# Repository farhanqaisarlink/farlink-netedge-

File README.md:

# FarLink

FarLink is a network performance monitoring platform built on the Raspberry Pi Compute Module 5 (CM5). It ships as two hardware variants that share a single codebase, plus a central dashboard server.

---

## Devices

### FarLink Go — with screen & push button

- On-demand speed test triggered by a push button; result shown on a 3.2" display
- Screen shows **only** the button-triggered speed test result — no other test output is displayed on-device
- Networking: DHCP by default, with a manual static IP option (`network_mode: dhcp | static`)
- Speed test engine: self-hosted **LibreSpeed** (configurable server address — no Ookla/speedtest.net, due to commercial licensing restrictions)
- Additional diagnostics (server-logged only, not shown on screen): `mtr`, `dig`, `curl`, `openssl`, `ping`, TCP port check
- Server can set a periodic test interval (15 min / 1 hour / 24 hours) in addition to the manual button trigger
- Results are saved locally with a timestamp; the server fetches the result file whenever the device is reachable and idle
- Device registers with the server

### FarLink Edge — headless, no screen or button

- Two units operate in **master/slave** configuration, running `iperf3` between them over a dedicated point-to-point link
- Physical connectivity: onboard RJ45 (ETH1) is used for uplink to the dashboard/internet; a USB-to-Ethernet adapter provides the dedicated master/slave link
- Same diagnostic suite as Go: `iperf3` (throughput / jitter / loss / retransmissions), `mtr`, `dig`, `curl`, `openssl`, `ping`, TCP port check
- Test schedule is set by the server; execution happens on the device
- Results are saved locally with a timestamp; the server fetches the result file whenever the device is reachable and idle
- Device registers with the server

### Shared codebase

Both devices run from **one common script**, not separate codebases. Hardware-specific behavior — screen output, push-button trigger, iPerf3 master/slave role — is enabled or disabled through configuration, so the same software runs on either hardware variant depending on which features are present.

---

## Server

- Receives device registrations and assigns device IDs
- Sets the periodic test interval (Go) or test schedule (Edge) per device
- Fetches each device's result file when the device is reachable and idle
- Combines fetched data into a report containing device ID, name, time, and per-test results

---

## Test tools

| Tool | Purpose |
|---|---|
| `librespeed-cli` | Internet speed test (Go) |
| `iperf3` | Throughput / jitter / loss / retransmissions, master/slave (Edge) |
| `mtr` | Path tracing |
| `dig` | DNS resolution timing |
| `curl` | HTTP/HTTPS response time |
| `openssl` | SSL/TLS certificate check |
| `ping` | ICMP latency |
| Python `socket` | TCP port reachability |

Install: `apt install iperf3 mtr dnsutils curl openssl`

---

## Hardware

- Raspberry Pi Compute Module 5 (non-wireless), single Gigabit Ethernet (RJ45), USB-C power, 3.2" ILI9341 display (Go only)
- Non-wireless CM5 is used deliberately to keep FCC/CE certification in the lower-cost unintentional-radiator path

---

## Out of scope for this phase

- ZTP provisioning / auto-registration beyond basic device registration
- AI-generated report summaries
- Ookla / speedtest.net as a test engine

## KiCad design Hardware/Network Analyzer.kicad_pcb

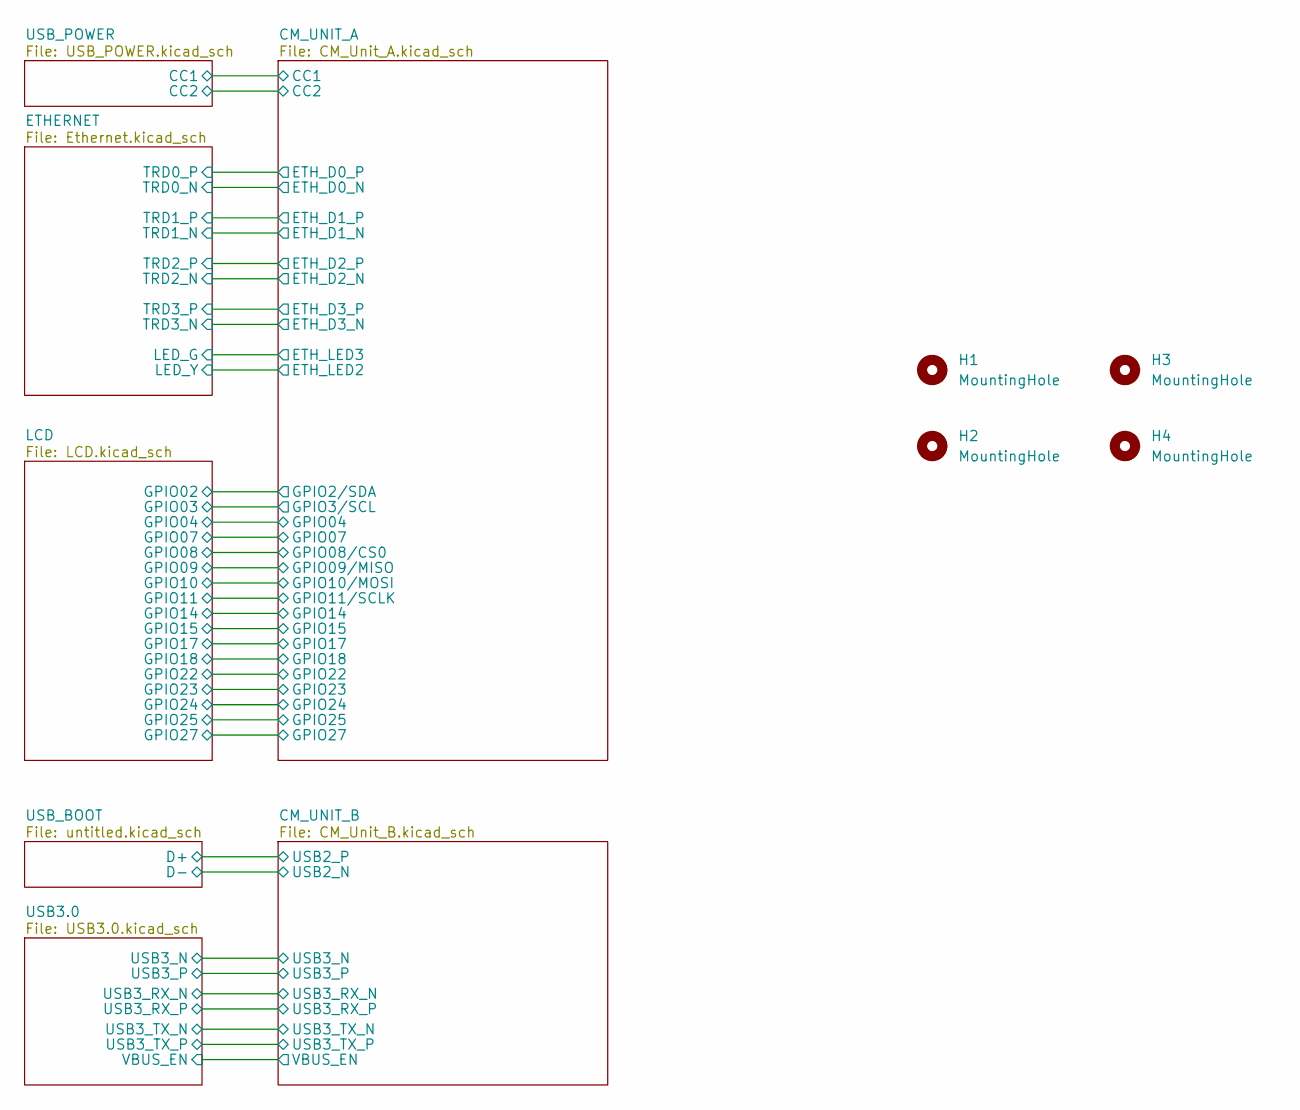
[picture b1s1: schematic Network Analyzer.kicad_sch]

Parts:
H1, H2, H3, H4: MountingHole; MountingHole_3.2mm_M3

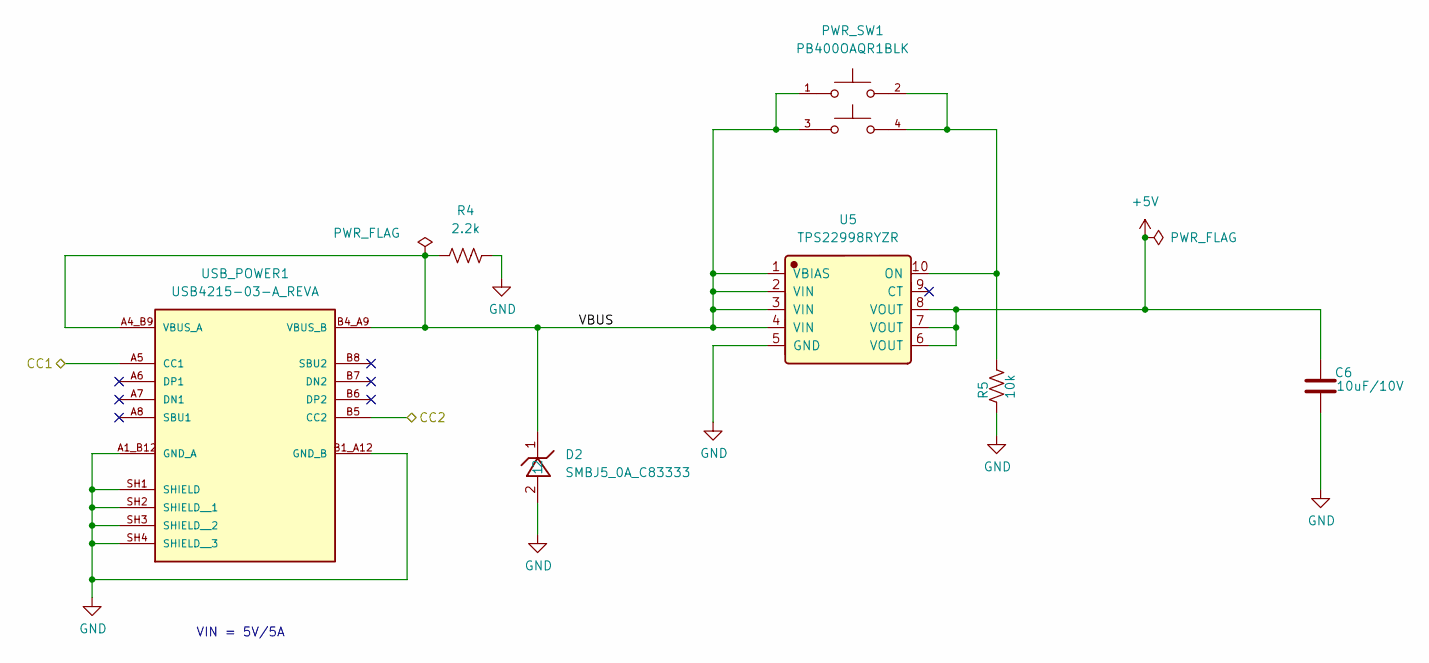
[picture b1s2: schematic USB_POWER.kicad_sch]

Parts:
C6: 10uF/10V; C_0603_1608Metric; Manufacturer_Part_Number GRM21BR61H106KE43L
D2: SMBJ5_0A_C83333; Manufacturer Part SMBJ5.0A; LCSC C83333
PWR_SW1: PB400OAQR1BLK; SW_PB400OAQR1BLK; PARTREV A
R4: 2.2k; R_0603_1608Metric_Pad0.98x0.95mm_HandSolder
R5: 10k; R_0603_1608Metric_Pad0.98x0.95mm_HandSolder; Part Description Resistor 1K M1005 1% 63mW
U5: TPS22998RYZR; Manufacturer Part TPS22998RYZR; LCSC C5220080
USB_POWER1: USB4215-03-A_REVA; GCT_USB4215-03-A_REVA; MPN USB4215-03-A

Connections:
+5V: C6.1, U5.6 (VOUT), U5.7 (VOUT), U5.8 (VOUT); also elsewhere on the board
/CM_UNIT_A/CC1: USB_POWER1.A5 (CC1); also elsewhere on the board
/CM_UNIT_A/CC2: USB_POWER1.B5 (CC2); also elsewhere on the board
/USB_POWER/VBUS: D2.1, PWR_SW1.1, PWR_SW1.3, R4.1, U5.1 (VBIAS), U5.2 (VIN), U5.3 (VIN), U5.4 (VIN), USB_POWER1.A4_B9 (VBUS_A), USB_POWER1.B4_A9 (VBUS_B)
GND: C6.2, D2.2, R4.2, R5.2, U5.5 (GND), USB_POWER1.A1_B12 (GND_A), USB_POWER1.B1_A12 (GND_B), USB_POWER1.SH1 (SHIELD), USB_POWER1.SH2 (SHIELD__1), USB_POWER1.SH3 (SHIELD__2), USB_POWER1.SH4 (SHIELD__3); also elsewhere on the board
unnamed: PWR_SW1.2, PWR_SW1.4, R5.1, U5.10 (ON)

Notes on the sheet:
VIN = 5V/5A

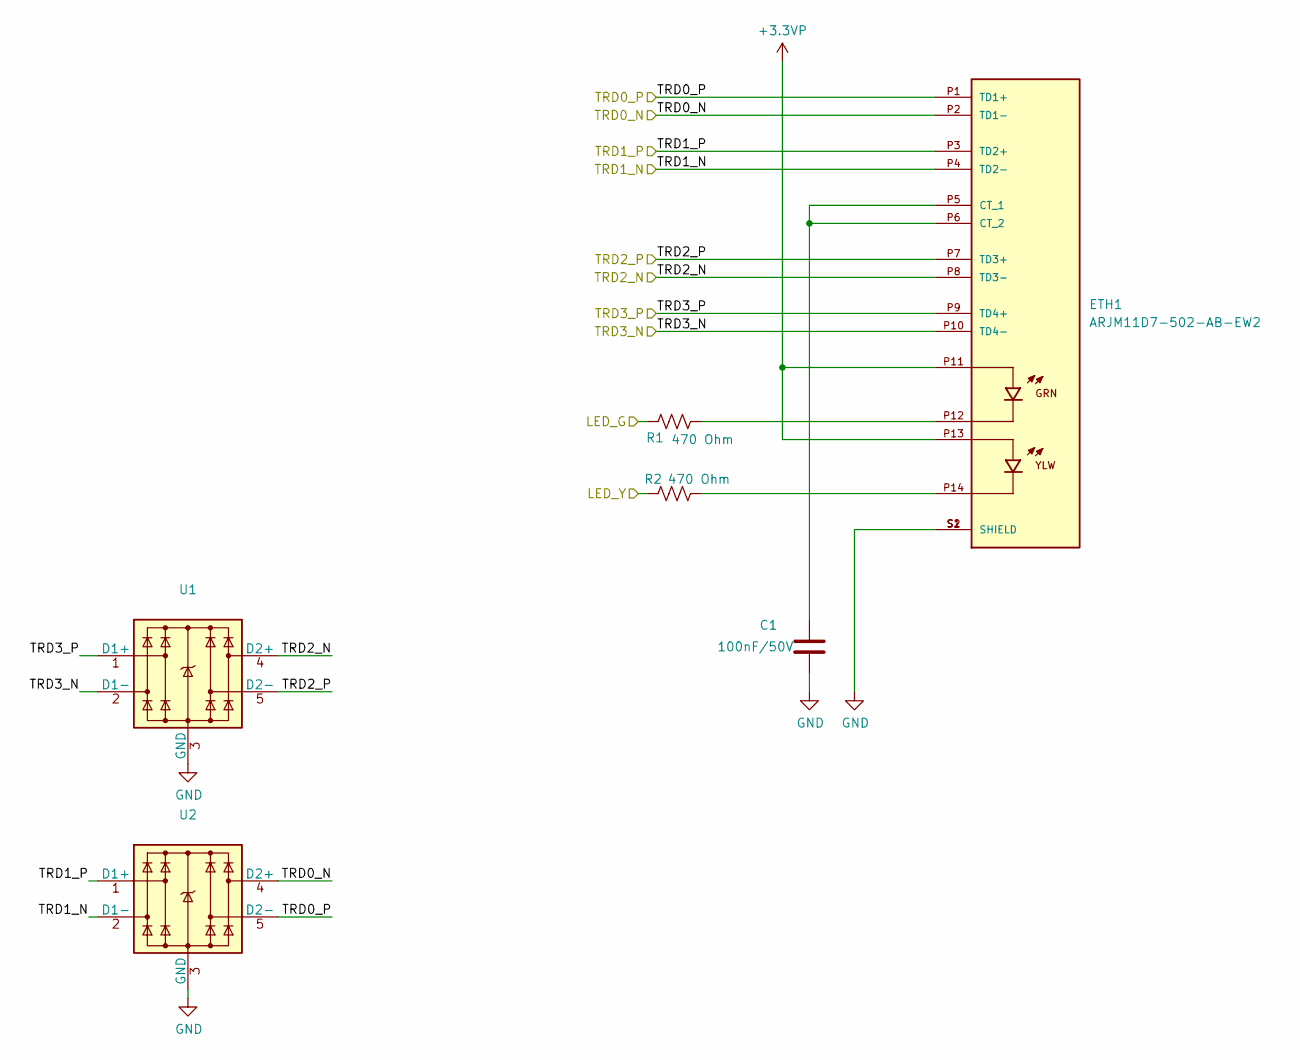
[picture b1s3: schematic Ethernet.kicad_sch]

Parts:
C1: 100nF/50V; C_0603_1608Metric; Manufacturer_Part_Number CL10B104KB8NNNC
ETH1: ARJM11D7-502-AB-EW2; ABRACON_ARJM11D7-502-AB-EW2; PARTREV 01-21-20
R1, R2: 470 Ohm; R_0603_1608Metric
U1, U2: TPD4EUSB30; USON-10_2.5x1.0mm_P0.5mm; Part Description Quad TVS diode for high speed signals (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

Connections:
+3.3VP: ETH1.P11, ETH1.P13; also elsewhere on the board
/CM_UNIT_A/ETH_LED2: R2.1; also elsewhere on the board
/CM_UNIT_A/ETH_LED3: R1.1; also elsewhere on the board
/ETHERNET/TRD0_N: ETH1.P2 (TD1-), U2.4 (D2+), U2.7; also elsewhere on the board
/ETHERNET/TRD0_P: ETH1.P1 (TD1+), U2.5 (D2-), U2.6; also elsewhere on the board
/ETHERNET/TRD1_N: ETH1.P4 (TD2-), U2.2 (D1-), U2.9; also elsewhere on the board
/ETHERNET/TRD1_P: ETH1.P3 (TD2+), U2.1 (D1+), U2.10; also elsewhere on the board
/ETHERNET/TRD2_N: ETH1.P8 (TD3-), U1.4 (D2+), U1.7; also elsewhere on the board
/ETHERNET/TRD2_P: ETH1.P7 (TD3+), U1.5 (D2-), U1.6; also elsewhere on the board
/ETHERNET/TRD3_N: ETH1.P10 (TD4-), U1.2 (D1-), U1.9; also elsewhere on the board
/ETHERNET/TRD3_P: ETH1.P9 (TD4+), U1.1 (D1+), U1.10; also elsewhere on the board
GND: C1.2, ETH1.S1 (SHIELD), ETH1.S2 (SHIELD), U1.3 (GND), U1.8 (GND), U2.3 (GND), U2.8 (GND); also elsewhere on the board
unnamed: C1.1, ETH1.P5 (CT_1), ETH1.P6 (CT_2)
unnamed: ETH1.P12, R1.2
unnamed: ETH1.P14, R2.2

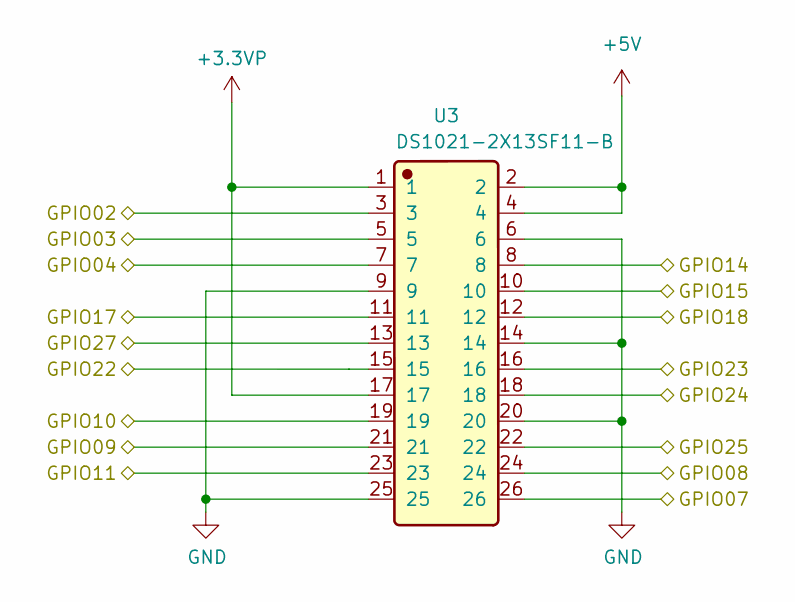
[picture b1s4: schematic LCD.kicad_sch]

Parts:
U3: DS1021-2X13SF11-B; Manufacturer Part DS1021-2x13SF11-B; LCSC C7430409

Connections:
+3.3VP: U3.1, U3.17; also elsewhere on the board
+5V: U3.2, U3.4; also elsewhere on the board
/CM_UNIT_A/CONSOLE_RXD: U3.10; also elsewhere on the board
/CM_UNIT_A/CONSOLE_TXD: U3.8; also elsewhere on the board
/CM_UNIT_A/GPIO2/SDA: U3.3; also elsewhere on the board
/CM_UNIT_A/GPIO3/SCL: U3.5; also elsewhere on the board
/CM_UNIT_A/GPIO04: U3.7; also elsewhere on the board
/CM_UNIT_A/GPIO07: U3.26; also elsewhere on the board
/CM_UNIT_A/GPIO08/CS0: U3.24; also elsewhere on the board
/CM_UNIT_A/GPIO09/MISO: U3.21; also elsewhere on the board
/CM_UNIT_A/GPIO10/MOSI: U3.19; also elsewhere on the board
/CM_UNIT_A/GPIO11/SCLK: U3.23; also elsewhere on the board
/CM_UNIT_A/GPIO17: U3.11; also elsewhere on the board
/CM_UNIT_A/GPIO18: U3.12; also elsewhere on the board
/CM_UNIT_A/GPIO22: U3.15; also elsewhere on the board
/CM_UNIT_A/GPIO23: U3.16; also elsewhere on the board
/CM_UNIT_A/GPIO24: U3.18; also elsewhere on the board
/CM_UNIT_A/GPIO25: U3.22; also elsewhere on the board
/CM_UNIT_A/GPIO27: U3.13; also elsewhere on the board
GND: U3.6, U3.9, U3.14, U3.20, U3.25; also elsewhere on the board

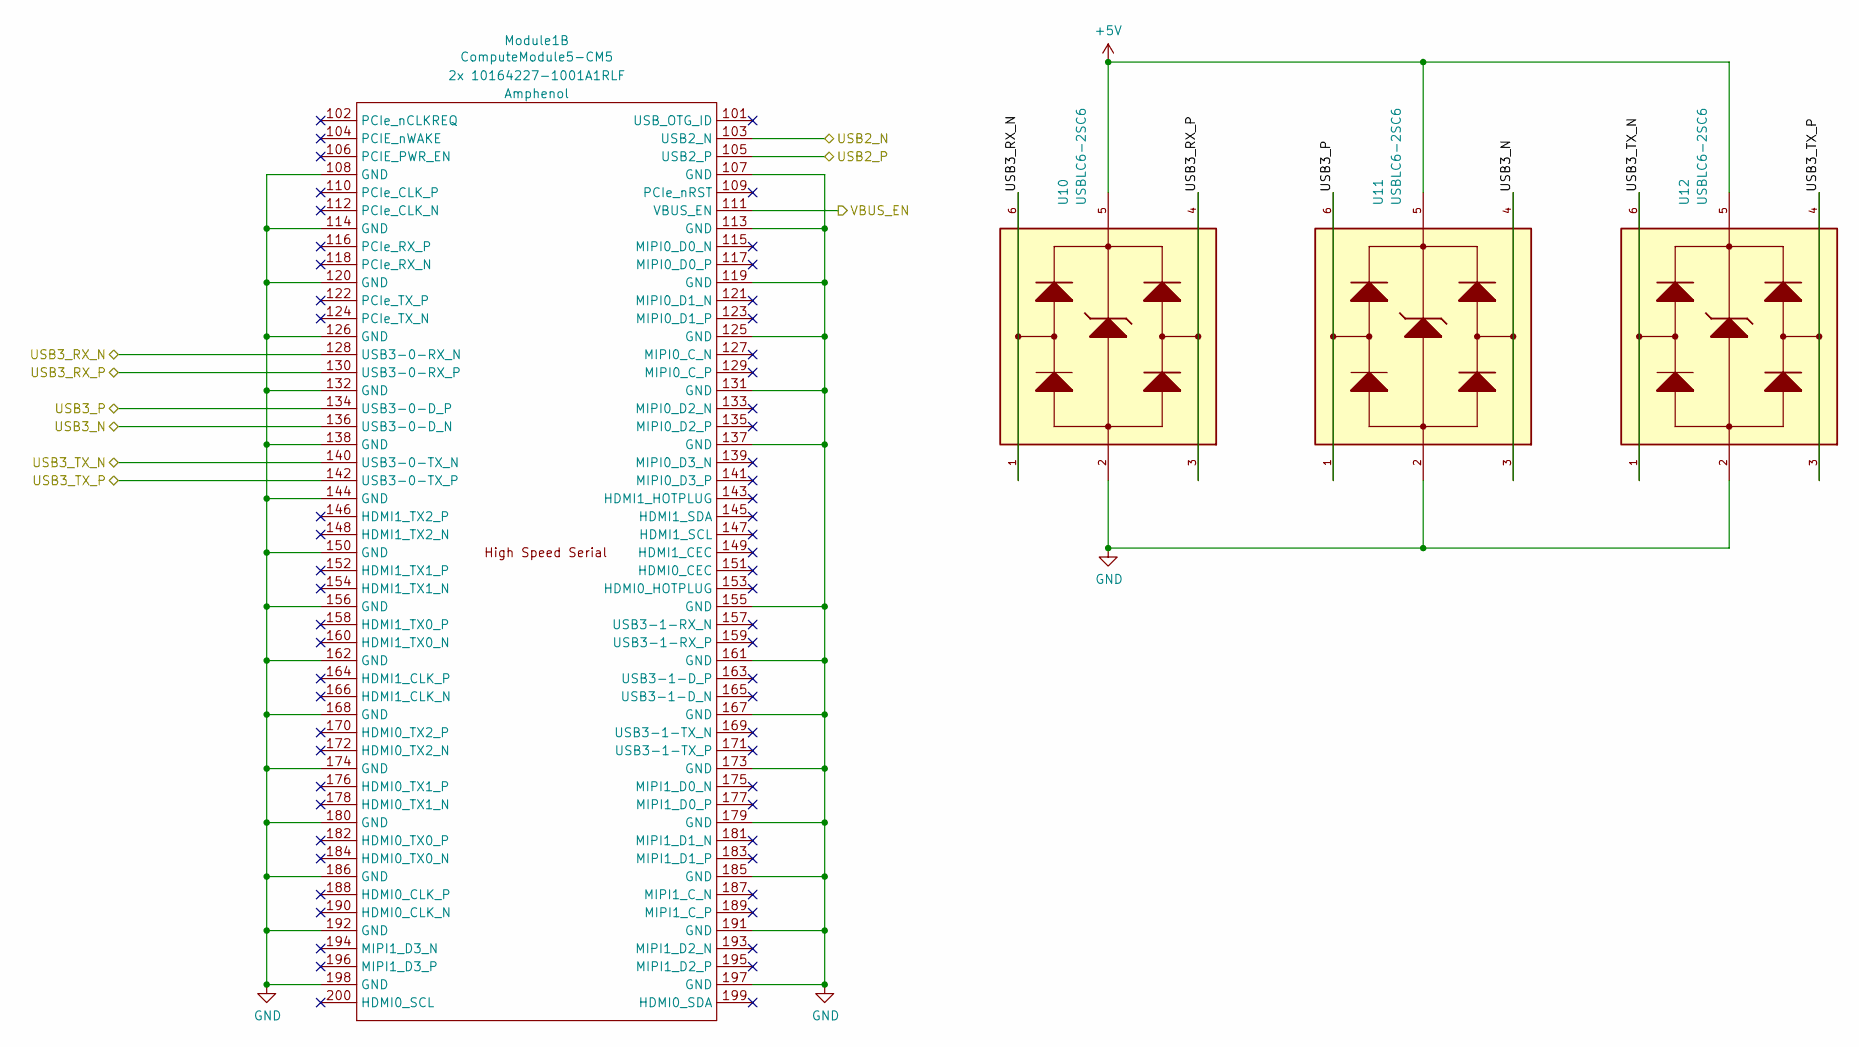
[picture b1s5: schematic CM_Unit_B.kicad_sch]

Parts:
Module1: ComputeModule5-CM5; Raspberry-Pi-5-Compute-Module; Part Description 100 Position Connector Receptacle, Cent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
U10, U11, U12: USBLC6-2SC6; SOT95P280X145-6N; Manufacturer Part USBLC6-2SC6

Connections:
+5V: U10.5, U11.5, U12.5; also elsewhere on the board
/CM_UNIT_B/USB3_N: Module1.136 (USB3-0-D_N), U11.3, U11.4; also elsewhere on the board
/CM_UNIT_B/USB3_P: Module1.134 (USB3-0-D_P), U11.1, U11.6; also elsewhere on the board
/CM_UNIT_B/USB3_RX_N: Module1.128 (USB3-0-RX_N), U10.1, U10.6; also elsewhere on the board
/CM_UNIT_B/USB3_RX_P: Module1.130 (USB3-0-RX_P), U10.3, U10.4; also elsewhere on the board
/CM_UNIT_B/USB3_TX_N: Module1.140 (USB3-0-TX_N), U12.1, U12.6; also elsewhere on the board
/CM_UNIT_B/USB3_TX_P: Module1.142 (USB3-0-TX_P), U12.3, U12.4; also elsewhere on the board
/CM_UNIT_B/VBUS_EN: Module1.111 (VBUS_EN); also elsewhere on the board
/USB_BOOT/D+: Module1.105 (USB2_P); also elsewhere on the board
/USB_BOOT/D-: Module1.103 (USB2_N); also elsewhere on the board
GND: Module1.107 (GND), Module1.108 (GND), Module1.113 (GND), Module1.114 (GND), Module1.119 (GND), Module1.120 (GND), Module1.125 (GND), Module1.126 (GND), Module1.131 (GND), Module1.132 (GND), Module1.137 (GND), Module1.138 (GND), Module1.144 (GND), Module1.150 (GND), Module1.155 (GND), Module1.156 (GND), Module1.161 (GND), Module1.162 (GND), Module1.167 (GND), Module1.168 (GND), Module1.173 (GND), Module1.174 (GND), Module1.179 (GND), Module1.180 (GND), Module1.185 (GND), Module1.186 (GND), Module1.191 (GND), Module1.192 (GND), Module1.197 (GND), Module1.198 (GND), U10.2, U11.2, U12.2; also elsewhere on the board

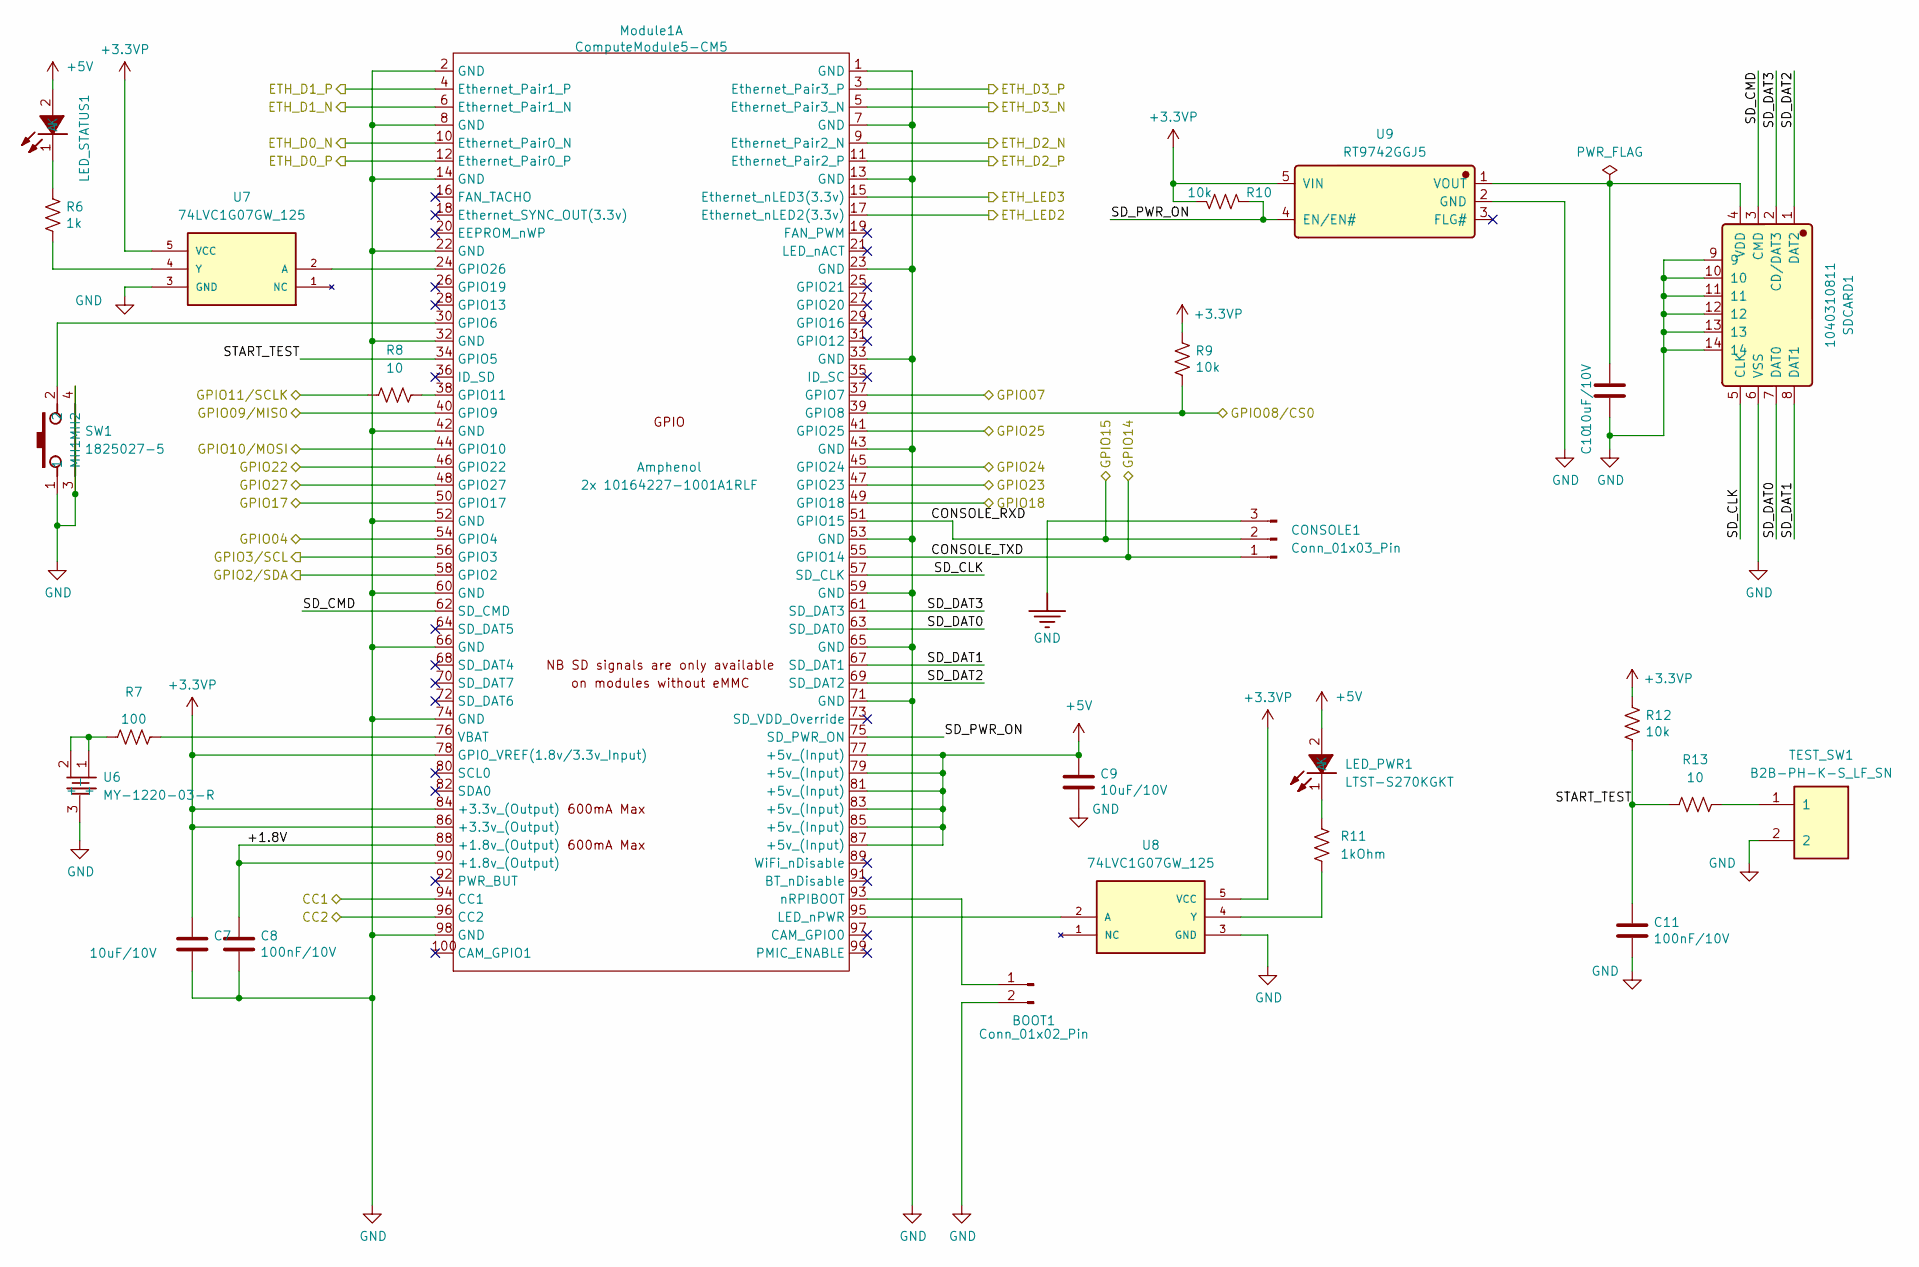
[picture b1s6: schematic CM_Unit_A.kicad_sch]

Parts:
BOOT1: Conn_01x02_Pin; PinHeader_1x02_P2.54mm_Vertical
C7, C9, C10: 10uF/10V; C_0603_1608Metric_Pad1.08x0.95mm_HandSolder
C8: 100nF/10V; C_0603_1608Metric_Pad1.08x0.95mm_HandSolder; Part Description 0.1uF 10% 16V Ceramic Capacitor X7R 040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
C11: 100nF/10V; C_0603_1608Metric; Part Description 0.1uF 10% 16V Ceramic Capacitor X7R 040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
CONSOLE1: Conn_01x03_Pin; PinHeader_1x03_P2.54mm_Vertical
LED_PWR1: LTST-S270KGKT; Manufacturer Part LTST-S270KGKT; LCSC C125113
LED_STATUS1: LTST-S270KRKT; Manufacturer Part LTST-S270KRKT; LCSC C125114
Module1: ComputeModule5-CM5; Raspberry-Pi-5-Compute-Module; Part Description 100 Position Connector Receptacle, Cent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
R6: 1k; R_0603_1608Metric; Part Description Resistor 1K M1005 1% 63mW
R7: 100; R_0603_1608Metric
R8, R13: 10; R_0603_1608Metric
R9: 10k; R_0603_1608Metric_Pad0.98x0.95mm_HandSolder; Part Description Resistor 1K M1005 1% 63mW
R10: 10k; R_0603_1608Metric
R11: 1kOhm; R_0603_1608Metric
R12: 10k; R_0603_1608Metric; Part Description Resistor 1K M1005 1% 63mW
SDCARD1: 1040310811; Manufacturer Part 1040310811; LCSC C585350
SW1: 1825027-5; Manufacturer Part 1825027-5; LCSC C86476
TEST_SW1: B2B-PH-K-S_LF_SN; Manufacturer Part B2B-PH-K-S(LF)(SN); LCSC C131337
U6: MY-1220-03-R; Manufacturer Part MY-1220-03-R; LCSC C964819
U7, U8: 74LVC1G07GW_125; IC_74LVC1G07GW_125; PARTREV 16
U9: RT9742GGJ5; Manufacturer Part RT9742GGJ5; LCSC C250547

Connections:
+3.3VP: C7.1, Module1.78 (GPIO_VREF(1.8v/3.3v_Input)), Module1.84 (+3.3v_(Output)), Module1.86 (+3.3v_(Output)), R9.1, R10.1, R12.1, U7.5 (VCC), U8.5 (VCC), U9.5 (VIN); also elsewhere on the board
+5V: C9.1, LED_PWR1.2 (A), LED_STATUS1.2 (A), Module1.77 (+5v_(Input)), Module1.79 (+5v_(Input)), Module1.81 (+5v_(Input)), Module1.83 (+5v_(Input)), Module1.85 (+5v_(Input)), Module1.87 (+5v_(Input)); also elsewhere on the board
/CM_UNIT_A/+1.8V: C8.1, Module1.88 (+1.8v_(Output)), Module1.90 (+1.8v_(Output))
/CM_UNIT_A/CC1: Module1.94 (CC1); also elsewhere on the board
/CM_UNIT_A/CC2: Module1.96 (CC2); also elsewhere on the board
/CM_UNIT_A/CONSOLE_RXD: CONSOLE1.2, Module1.51 (GPIO15); also elsewhere on the board
/CM_UNIT_A/CONSOLE_TXD: CONSOLE1.1, Module1.55 (GPIO14); also elsewhere on the board
/CM_UNIT_A/ETH_LED2: Module1.17 (Ethernet_nLED2(3.3v)); also elsewhere on the board
/CM_UNIT_A/ETH_LED3: Module1.15 (Ethernet_nLED3(3.3v)); also elsewhere on the board
/CM_UNIT_A/GPIO2/SDA: Module1.58 (GPIO2); also elsewhere on the board
/CM_UNIT_A/GPIO3/SCL: Module1.56 (GPIO3); also elsewhere on the board
/CM_UNIT_A/GPIO04: Module1.54 (GPIO4); also elsewhere on the board
/CM_UNIT_A/GPIO07: Module1.37 (GPIO7); also elsewhere on the board
/CM_UNIT_A/GPIO08/CS0: Module1.39 (GPIO8), R9.2; also elsewhere on the board
/CM_UNIT_A/GPIO09/MISO: Module1.40 (GPIO9); also elsewhere on the board
/CM_UNIT_A/GPIO10/MOSI: Module1.44 (GPIO10); also elsewhere on the board
/CM_UNIT_A/GPIO11/SCLK: R8.1; also elsewhere on the board
/CM_UNIT_A/GPIO17: Module1.50 (GPIO17); also elsewhere on the board
/CM_UNIT_A/GPIO18: Module1.49 (GPIO18); also elsewhere on the board
/CM_UNIT_A/GPIO22: Module1.46 (GPIO22); also elsewhere on the board
/CM_UNIT_A/GPIO23: Module1.47 (GPIO23); also elsewhere on the board
/CM_UNIT_A/GPIO24: Module1.45 (GPIO24); also elsewhere on the board
/CM_UNIT_A/GPIO25: Module1.41 (GPIO25); also elsewhere on the board
/CM_UNIT_A/GPIO27: Module1.48 (GPIO27); also elsewhere on the board
/CM_UNIT_A/SD_CLK: Module1.57 (SD_CLK), SDCARD1.5 (CLK)
/CM_UNIT_A/SD_CMD: Module1.62 (SD_CMD), SDCARD1.3 (CMD)
/CM_UNIT_A/SD_DAT0: Module1.63 (SD_DAT0), SDCARD1.7 (DAT0)
/CM_UNIT_A/SD_DAT1: Module1.67 (SD_DAT1), SDCARD1.8 (DAT1)
/CM_UNIT_A/SD_DAT2: Module1.69 (SD_DAT2), SDCARD1.1 (DAT2)
/CM_UNIT_A/SD_DAT3: Module1.61 (SD_DAT3), SDCARD1.2 (CD/DAT3)
/CM_UNIT_A/SD_PWR_ON: Module1.75 (SD_PWR_ON), R10.2, U9.4 (EN/EN#)
/CM_UNIT_A/START_TEST: C11.1, Module1.34 (GPIO5), R12.2, R13.1
/ETHERNET/TRD0_N: Module1.10 (Ethernet_Pair0_N); also elsewhere on the board
/ETHERNET/TRD0_P: Module1.12 (Ethernet_Pair0_P); also elsewhere on the board
/ETHERNET/TRD1_N: Module1.6 (Ethernet_Pair1_N); also elsewhere on the board
/ETHERNET/TRD1_P: Module1.4 (Ethernet_Pair1_P); also elsewhere on the board
/ETHERNET/TRD2_N: Module1.9 (Ethernet_Pair2_N); also elsewhere on the board
/ETHERNET/TRD2_P: Module1.11 (Ethernet_Pair2_P); also elsewhere on the board
/ETHERNET/TRD3_N: Module1.5 (Ethernet_Pair3_N); also elsewhere on the board
/ETHERNET/TRD3_P: Module1.3 (Ethernet_Pair3_P); also elsewhere on the board
GND: BOOT1.2, C7.2, C8.2, C9.2, C10.2, C11.2, CONSOLE1.3, Module1.1 (GND), Module1.2 (GND), Module1.7 (GND), Module1.8 (GND), Module1.13 (GND), Module1.14 (GND), Module1.22 (GND), Module1.23 (GND), Module1.32 (GND), Module1.33 (GND), Module1.42 (GND), Module1.43 (GND), Module1.52 (GND), Module1.53 (GND), Module1.59 (GND), Module1.60 (GND), Module1.65 (GND), Module1.66 (GND), Module1.71 (GND), Module1.74 (GND), Module1.98 (GND), SDCARD1.6 (VSS), SDCARD1.9, SDCARD1.10, SDCARD1.11, SDCARD1.12, SDCARD1.13, SDCARD1.14, SW1.1, SW1.3 (MH1), SW1.4 (MH2), TEST_SW1.2, U6.3 (-), U7.3 (GND), U8.3 (GND), U9.2 (GND); also elsewhere on the board
unnamed: BOOT1.1, Module1.93 (nRPIBOOT)
unnamed: LED_PWR1.1 (K), R11.1
unnamed: LED_STATUS1.1 (K), R6.1
unnamed: Module1.30 (GPIO6), SW1.2
unnamed: Module1.38 (GPIO11), R8.2
unnamed: Module1.24 (GPIO26), U7.2 (A)
unnamed: Module1.95 (LED_nPWR), U8.2 (A)
unnamed: Module1.76 (VBAT), R7.2
unnamed: R7.1, U6.1 (+), U6.2 (+)
unnamed: R13.2, TEST_SW1.1
unnamed: C10.1, SDCARD1.4 (VDD), U9.1 (VOUT)
unnamed: R6.2, U7.4 (Y)
unnamed: R11.2, U8.4 (Y)

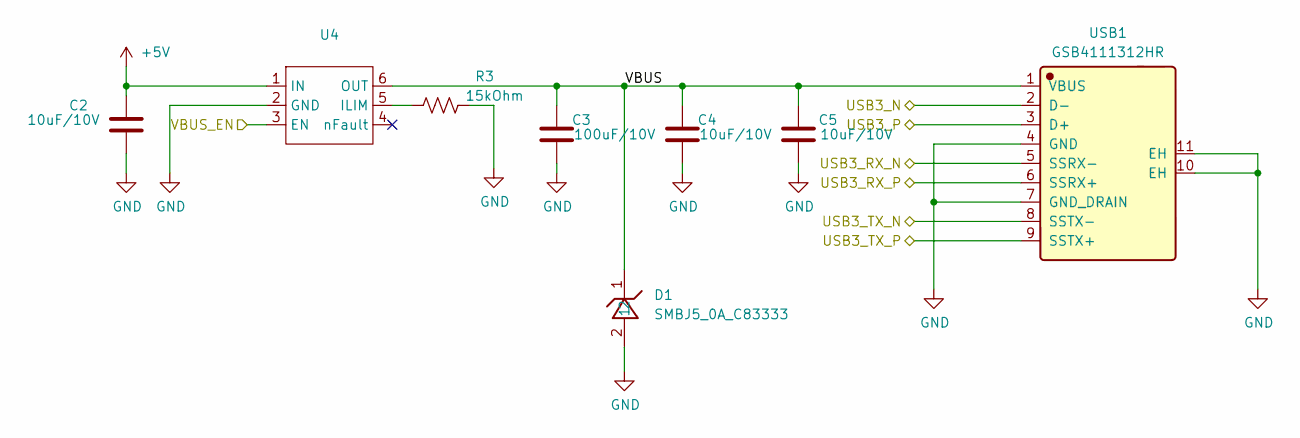
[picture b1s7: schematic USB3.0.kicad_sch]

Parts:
C2, C4, C5: 10uF/10V; C_0603_1608Metric; Manufacturer_Part_Number GRM21BR61H106KE43L
C3: 100uF/10V; C_1210_3225Metric; Manufacturer_Part_Number GRM21BR61H106KE43L
D1: SMBJ5_0A_C83333; Manufacturer Part SMBJ5.0A; LCSC C83333
R3: 15kOhm; R_0603_1608Metric
U4: AP22653W6-7; SOT-23-6; Part Description Power Switch/Driver 1:1 P-Channel 2.1A 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
USB1: GSB4111312HR; Manufacturer Part GSB4111312HR; LCSC C5429382

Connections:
+5V: C2.1, U4.1 (IN); also elsewhere on the board
/CM_UNIT_B/USB3_N: USB1.2 (D-); also elsewhere on the board
/CM_UNIT_B/USB3_P: USB1.3 (D+); also elsewhere on the board
/CM_UNIT_B/USB3_RX_N: USB1.5 (SSRX-); also elsewhere on the board
/CM_UNIT_B/USB3_RX_P: USB1.6 (SSRX+); also elsewhere on the board
/CM_UNIT_B/USB3_TX_N: USB1.8 (SSTX-); also elsewhere on the board
/CM_UNIT_B/USB3_TX_P: USB1.9 (SSTX+); also elsewhere on the board
/CM_UNIT_B/VBUS_EN: U4.3 (EN); also elsewhere on the board
/USB3.0/VBUS: C3.1, C4.1, C5.1, D1.1, U4.6 (OUT), USB1.1 (VBUS)
GND: C2.2, C3.2, C4.2, C5.2, D1.2, R3.2, U4.2 (GND), USB1.4 (GND), USB1.7 (GND_DRAIN), USB1.10 (EH), USB1.11 (EH); also elsewhere on the board
unnamed: R3.1, U4.5 (ILIM)

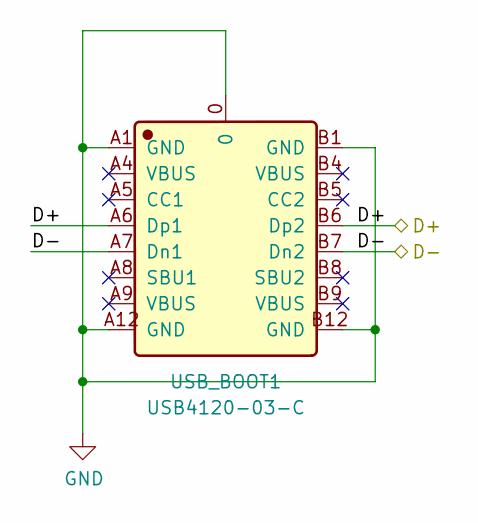
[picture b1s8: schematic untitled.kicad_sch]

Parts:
USB_BOOT1: USB4120-03-C; Manufacturer Part USB4120-03-C; LCSC C3445864

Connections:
/USB_BOOT/D+: USB_BOOT1.A6 (Dp1), USB_BOOT1.B6 (Dp2); also elsewhere on the board
/USB_BOOT/D-: USB_BOOT1.A7 (Dn1), USB_BOOT1.B7 (Dn2); also elsewhere on the board
GND: USB_BOOT1.0, USB_BOOT1.A1 (GND), USB_BOOT1.A12 (GND), USB_BOOT1.B1 (GND), USB_BOOT1.B12 (GND); also elsewhere on the board

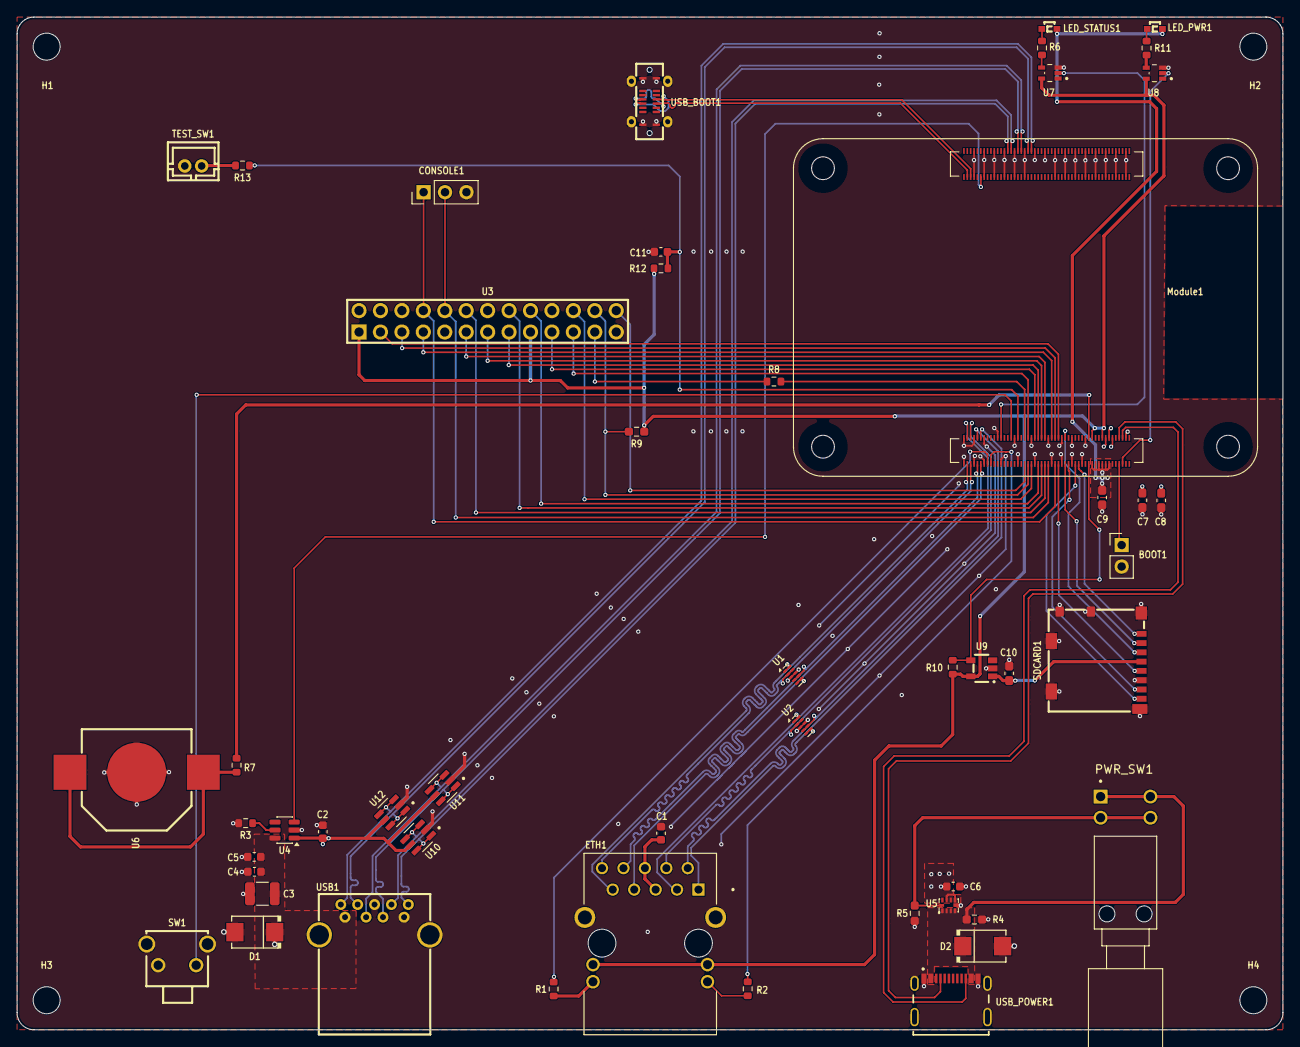
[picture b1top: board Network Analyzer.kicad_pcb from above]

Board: 4 copper layers, 150.0 x 120.0 mm, 55 parts (0 on the bottom side), 70 nets.
